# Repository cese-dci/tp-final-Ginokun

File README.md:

## Trabajo práctico final de la asignatura DCI ##
Este repositorio contiene el trabajo práctico final para la asignatura de Diseño de Circuitos Impresos de la carrera de posgrado de FIUBA.

* Autor: Matias Meghinasso
* Título corto del trabajo:  Réplica Módulo RTC DS3231
* Descripción:  Diseño esquematico en KICAD del circuito RTC DS3231 con memoria EEPROM incorporada.

## Licencia de este trabajo ##
GPL V3.0

## Estructura del TP FINAL ##

Se propone y se pide utilizar la siguiente estructura.

* doc: Toda la información sobre el circuito, principalmente de autoría o procesamiento propio. Por ejemplo:
  * Notas de ingeniería propias.
  * Notas de aplicación propias.
  * Estudios previos, estado del arte, resumen de las investigaciones.
  * Notas con cálculos.
  * Dibujos adicionales.
  * Fotos de los prototipos.
  * Presupuestos, cotizaciones.
* info: Toda la iformación recolectada, principalmente de terceros, como por ejemplo:
  * Hojas de datos.
  * Notas de aplicación.
  * Info de productos comerciales.
  * Info en internet.
* pcb: Archivos de diseño esquemático y pcb.

Dependiendo la magnitud del proyecto, tendremos más o menos información en estos directorios. 
Revisar los README.md en cada directorio para conocer las pautas de cada uno para este TP.

NOTA: El alumno puede y debe borrar de este archivo todo lo que considere necesario, por ejemplo las aclaraciones del docente y esta misma nota.

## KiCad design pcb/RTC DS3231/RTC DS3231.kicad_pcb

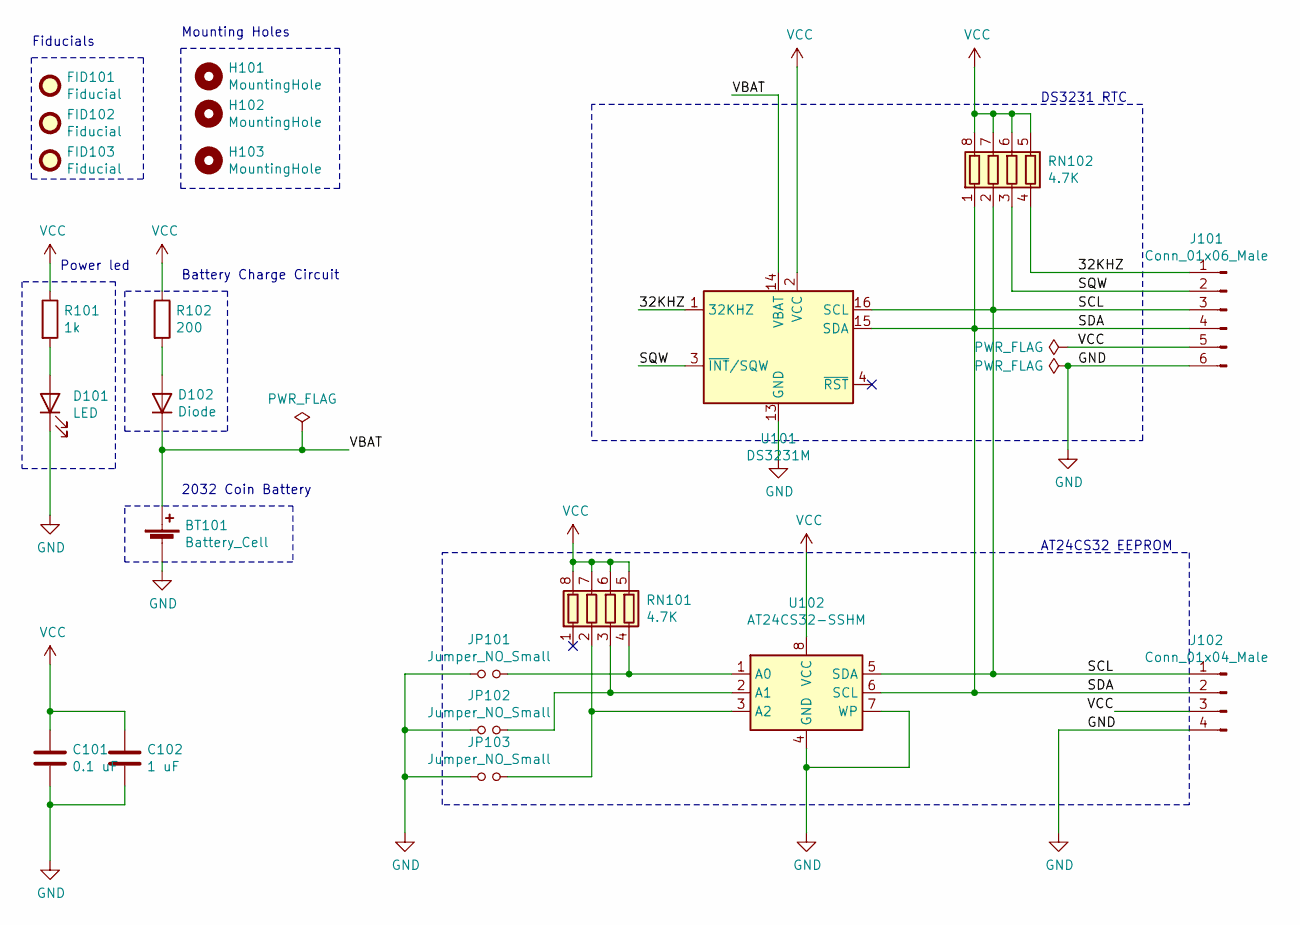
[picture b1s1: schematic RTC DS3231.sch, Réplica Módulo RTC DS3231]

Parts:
BT101: Battery_Cell; BatteryHolder_Keystone_1058_1x2032
C101: 0.1 uF; C_0805_2012Metric
C102: 1 uF; C_0805_2012Metric
D101: LED; LED_0805_2012Metric_Castellated
D102: Diode; D_0805_2012Metric
FID101, FID102, FID103: Fiducial; Fiducial_0.5mm_Mask1mm
H101, H102, H103: MountingHole; MountingHole_2.5mm_Pad_TopOnly
J101: Conn_01x06_Male; PinSocket_1x06_P2.54mm_Vertical
J102: Conn_01x04_Male; PinSocket_1x04_P2.54mm_Vertical
JP101, JP102, JP103: Jumper_NO_Small; TestPoint_2Pads_Pitch2.54mm_Drill0.8mm
R101: 1k; R_0805_2012Metric
R102: 200; R_0805_2012Metric
RN101, RN102: 4.7K; R_Array_Concave_4x0603
U101: DS3231M; SOIC-16W_7.5x10.3mm_P1.27mm
U102: AT24CS32-SSHM; SOIC-8_3.9x4.9mm_P1.27mm

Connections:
/32KHZ: J101.1, RN102.4 (R4.1), U101.1 (32KHZ)
/SCL: J101.3, J102.1, RN102.2 (R2.1), U101.16 (SCL), U102.5 (SDA)
/SDA: J101.4, J102.2, RN102.1 (R1.1), U101.15 (SDA), U102.6 (SCL)
/SQW: J101.2, RN102.3 (R3.1), U101.3 (~INT~/SQW)
/VBAT: BT101.1 (+), D102.1 (K), U101.14 (VBAT)
GND: BT101.2 (-), C101.2, C102.2, D101.1 (K), J101.6, J102.4, JP101.1, JP102.1, JP103.1, U101.5 (GND), U101.6 (GND), U101.7 (GND), U101.8 (GND), U101.9 (GND), U101.10 (GND), U101.11 (GND), U101.12 (GND), U101.13 (GND), U102.4 (GND), U102.7 (WP)
unnamed: D101.2 (A), R101.2
unnamed: D102.2 (A), R102.2
unnamed: JP101.2, RN101.4 (R4.1), U102.1 (A0)
unnamed: JP102.2, RN101.3 (R3.1), U102.2 (A1)
unnamed: JP103.2, RN101.2 (R2.1), U102.3 (A2)
VCC: C101.1, C102.1, J101.5, J102.3, R101.1, R102.1, RN101.5 (R4.2), RN101.6 (R3.2), RN101.7 (R2.2), RN101.8 (R1.2), RN102.5 (R4.2), RN102.6 (R3.2), RN102.7 (R2.2), RN102.8 (R1.2), U101.2 (VCC), U102.8 (VCC)

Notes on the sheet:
Battery Charge Circuit
Power led
DS3231 RTC
AT24CS32 EEPROM
2032 Coin Battery
Fiducials
Mounting Holes

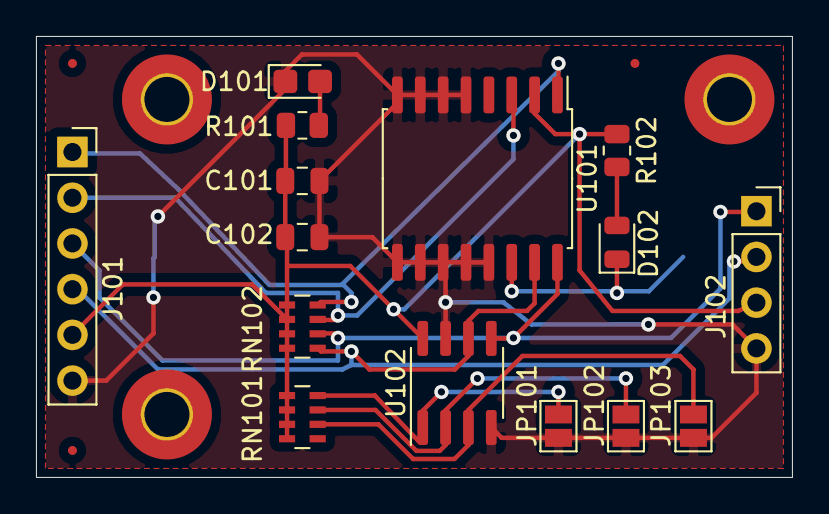
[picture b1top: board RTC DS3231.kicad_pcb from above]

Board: 2 copper layers, 42.0 x 24.5 mm, 22 parts (1 on the bottom side), 12 nets.

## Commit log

2021-09-16 schematic components added
2021-09-21 Updated schematic.
2021-09-21 Updates schematic to pass ERC.
2021-09-21 Modified folders.
2021-09-22 Modificación esquemático.
    Se agregaron los fiduciales y los recuadros que aclaran a que corresponde cada parte del circuito.
2021-09-22 Reordered components.
2021-09-23 Updates schematic and footprints.
2021-09-23 Updated datasheets.
2021-09-23 Mounting Holes added.
2021-09-24 Deleted images and updated schematic.
2021-10-13 Ruteos PCB.
2021-10-14 Silks.
    Se acomodaron y agregaron las serigrafias en el PCB.
2021-10-14 Anotaciones para fabricación.
    Se agregaron las anotaciones para el fabricante del PCB.

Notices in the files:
pcb/RTC DS3231/RTC DS3231.kicad_pcb:
Licence: GPL V3.0
pcb/RTC DS3231/RTC DS3231.sch:
License: GPL V3.0
